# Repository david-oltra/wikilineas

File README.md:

SIGUELINEAS PARA EL CURSO DE LABORATORIO GLUON
--------------------------------------------------------------

BOM

ESP32-DevKitC-32 (ESP-32-CP2102) <br>
https://es.aliexpress.com/item/1005005970816555.html

TB6612 -> CONTROLADOR MOTORES <br>
https://es.aliexpress.com/item/1005005839383613.html

CD74HC4067 -> MULTIPLEXOR <br>
https://es.aliexpress.com/item/1005005199818750.html

QRE1113 -> ARRAY SENSORES <br>
https://es.aliexpress.com/item/1005006408285450.html

SWITCH (6x6x5mm) <br>
https://es.aliexpress.com/item/32912263133.html

CONECTORES (JST PH 2,0) <br>
https://es.aliexpress.com/item/4001236530594.html

RESISTENCIA SMD 0805 <br>
https://es.aliexpress.com/item/1005005600798857.html

RESISTENCIA TH <br>
https://es.aliexpress.com/item/32952657927.html

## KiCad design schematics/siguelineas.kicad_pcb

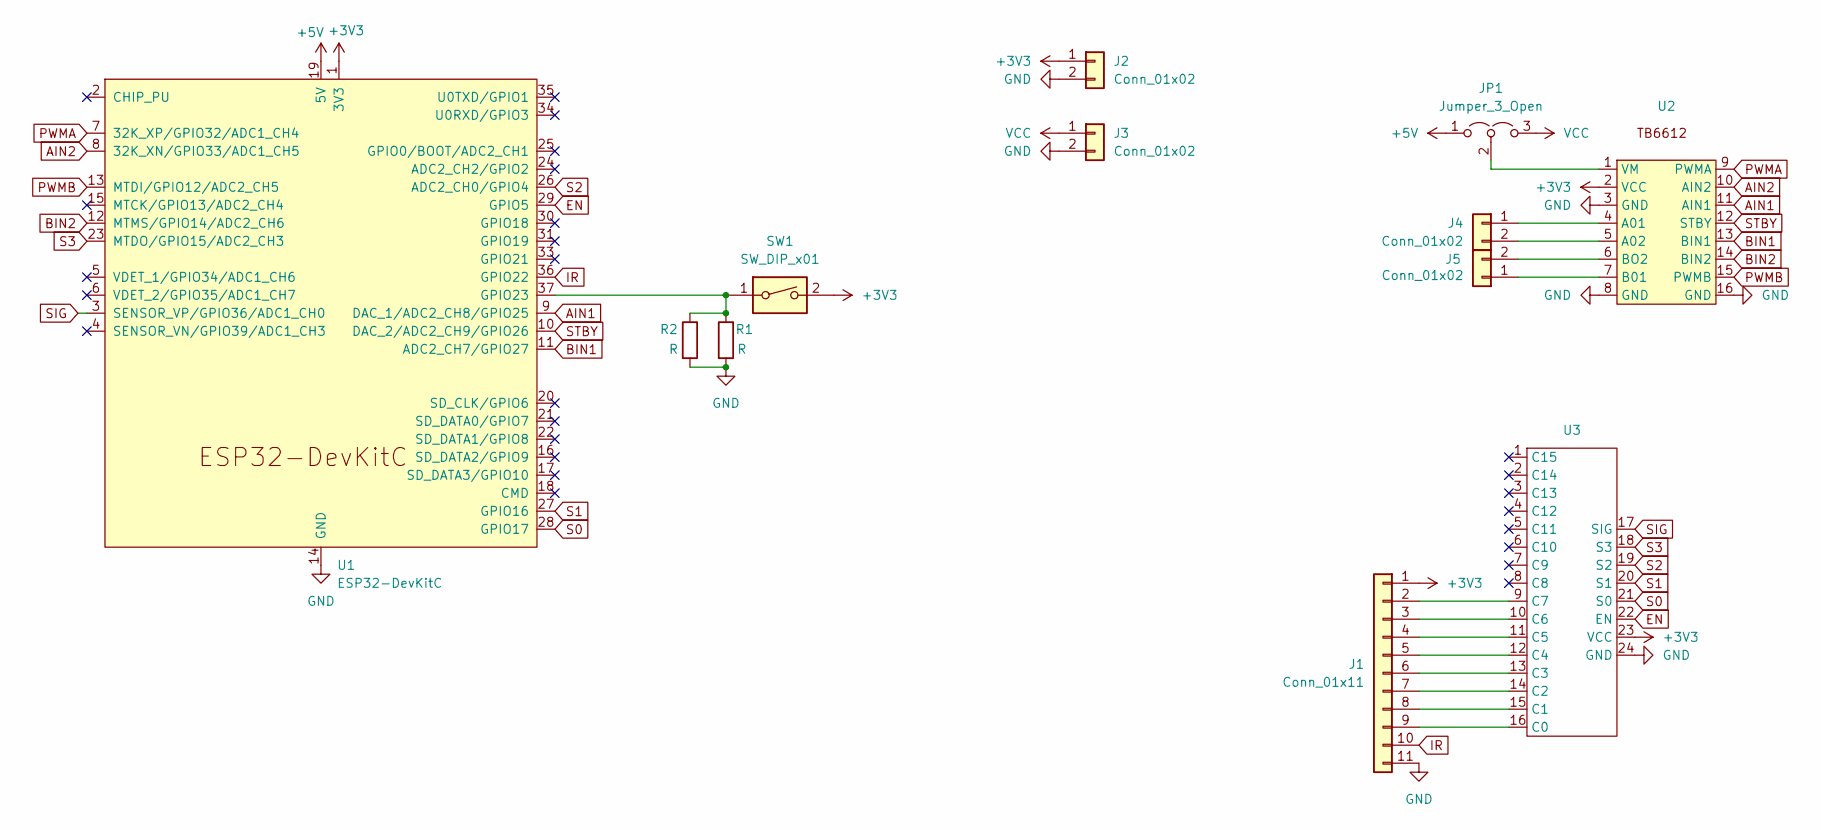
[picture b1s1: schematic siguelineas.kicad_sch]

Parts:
J1: Conn_01x11; PinHeader_1x11_P2.54mm_Vertical
J2, J3, J4, J5: Conn_01x02; JST_PH_B2B-PH-K_1x02_P2.00mm_Vertical
JP1: Jumper_3_Open; PinHeader_1x03_P2.54mm_Vertical
R1: R; R_Axial_DIN0207_L6.3mm_D2.5mm_P10.16mm_Horizontal
R2: R; R_0805_2012Metric_Pad1.20x1.40mm_HandSolder
SW1: SW_DIP_x01; SW_PUSH_6mm_H5mm
U1: ESP32-DevKitC
U2: TB6612
U3: CD74HC4067

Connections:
+3V3: J1.1, J2.1, SW1.2, U1.1 (3V3), U2.2 (VCC), U3.23 (VCC)
+5V: JP1.1 (A), U1.19 (5V)
AIN1: U1.9 (DAC_1/ADC2_CH8/GPIO25), U2.11 (AIN1)
AIN2: U1.8 (32K_XN/GPIO33/ADC1_CH5), U2.10 (AIN2)
BIN1: U1.11 (ADC2_CH7/GPIO27), U2.13 (BIN1)
BIN2: U1.12 (MTMS/GPIO14/ADC2_CH6), U2.14 (BIN2)
EN: U1.29 (GPIO5), U3.22 (EN)
GND: J1.11, J2.2, J3.2, R1.2, R2.2, U1.14 (GND), U1.32 (GND), U1.38 (GND), U2.3 (GND), U2.8 (GND), U2.16 (GND), U3.24 (GND)
IR: J1.10, U1.36 (GPIO22)
unnamed: J1.2, U3.9 (C7)
unnamed: J1.3, U3.10 (C6)
unnamed: J1.4, U3.11 (C5)
unnamed: J1.5, U3.12 (C4)
unnamed: J1.6, U3.13 (C3)
unnamed: J1.7, U3.14 (C2)
unnamed: J1.8, U3.15 (C1)
unnamed: J1.9, U3.16 (C0)
unnamed: J4.1, U2.4 (A01)
unnamed: J4.2, U2.5 (A02)
unnamed: J5.1, U2.7 (B01)
unnamed: J5.2, U2.6 (BO2)
unnamed: JP1.2 (C), U2.1 (VM)
unnamed: R1.1, R2.1, SW1.1, U1.37 (GPIO23)
PWMA: U1.7 (32K_XP/GPIO32/ADC1_CH4), U2.9 (PWMA)
PWMB: U1.13 (MTDI/GPIO12/ADC2_CH5), U2.15 (PWMB)
S0: U1.28 (GPIO17), U3.21 (S0)
S1: U1.27 (GPIO16), U3.20 (S1)
S2: U1.26 (ADC2_CH0/GPIO4), U3.19 (S2)
S3: U1.23 (MTDO/GPIO15/ADC2_CH3), U3.18 (S3)
SIG: U1.3 (SENSOR_VP/GPIO36/ADC1_CH0), U3.17 (SIG)
STBY: U1.10 (DAC_2/ADC2_CH9/GPIO26), U2.12 (STBY)
VCC: J3.1, JP1.3 (B)

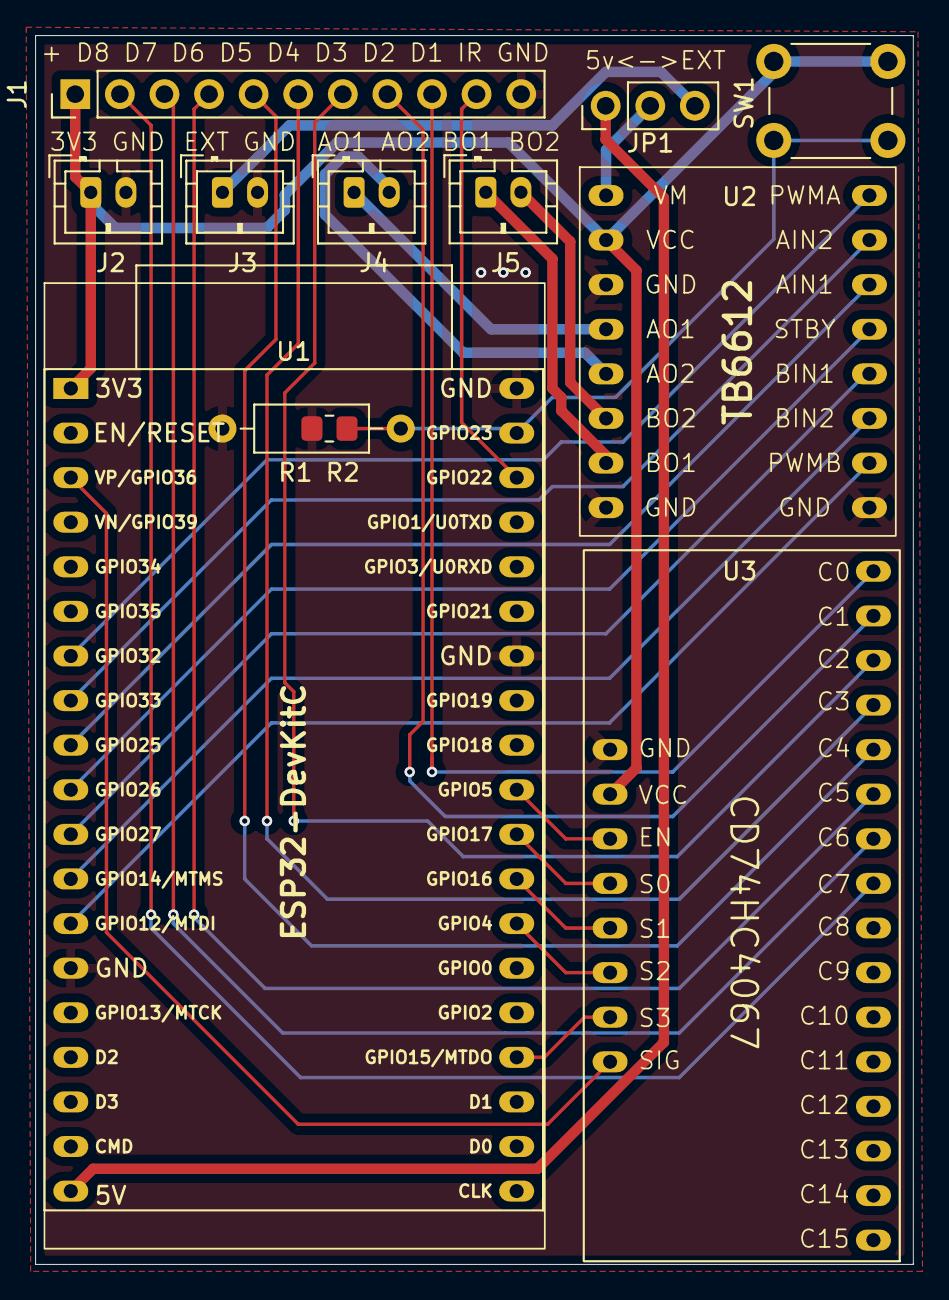
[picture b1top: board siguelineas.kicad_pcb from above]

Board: 2 copper layers, 50.0 x 70.0 mm, 12 parts (0 on the bottom side), 32 nets.

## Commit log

2024-03-26 Add CD74HC4067
